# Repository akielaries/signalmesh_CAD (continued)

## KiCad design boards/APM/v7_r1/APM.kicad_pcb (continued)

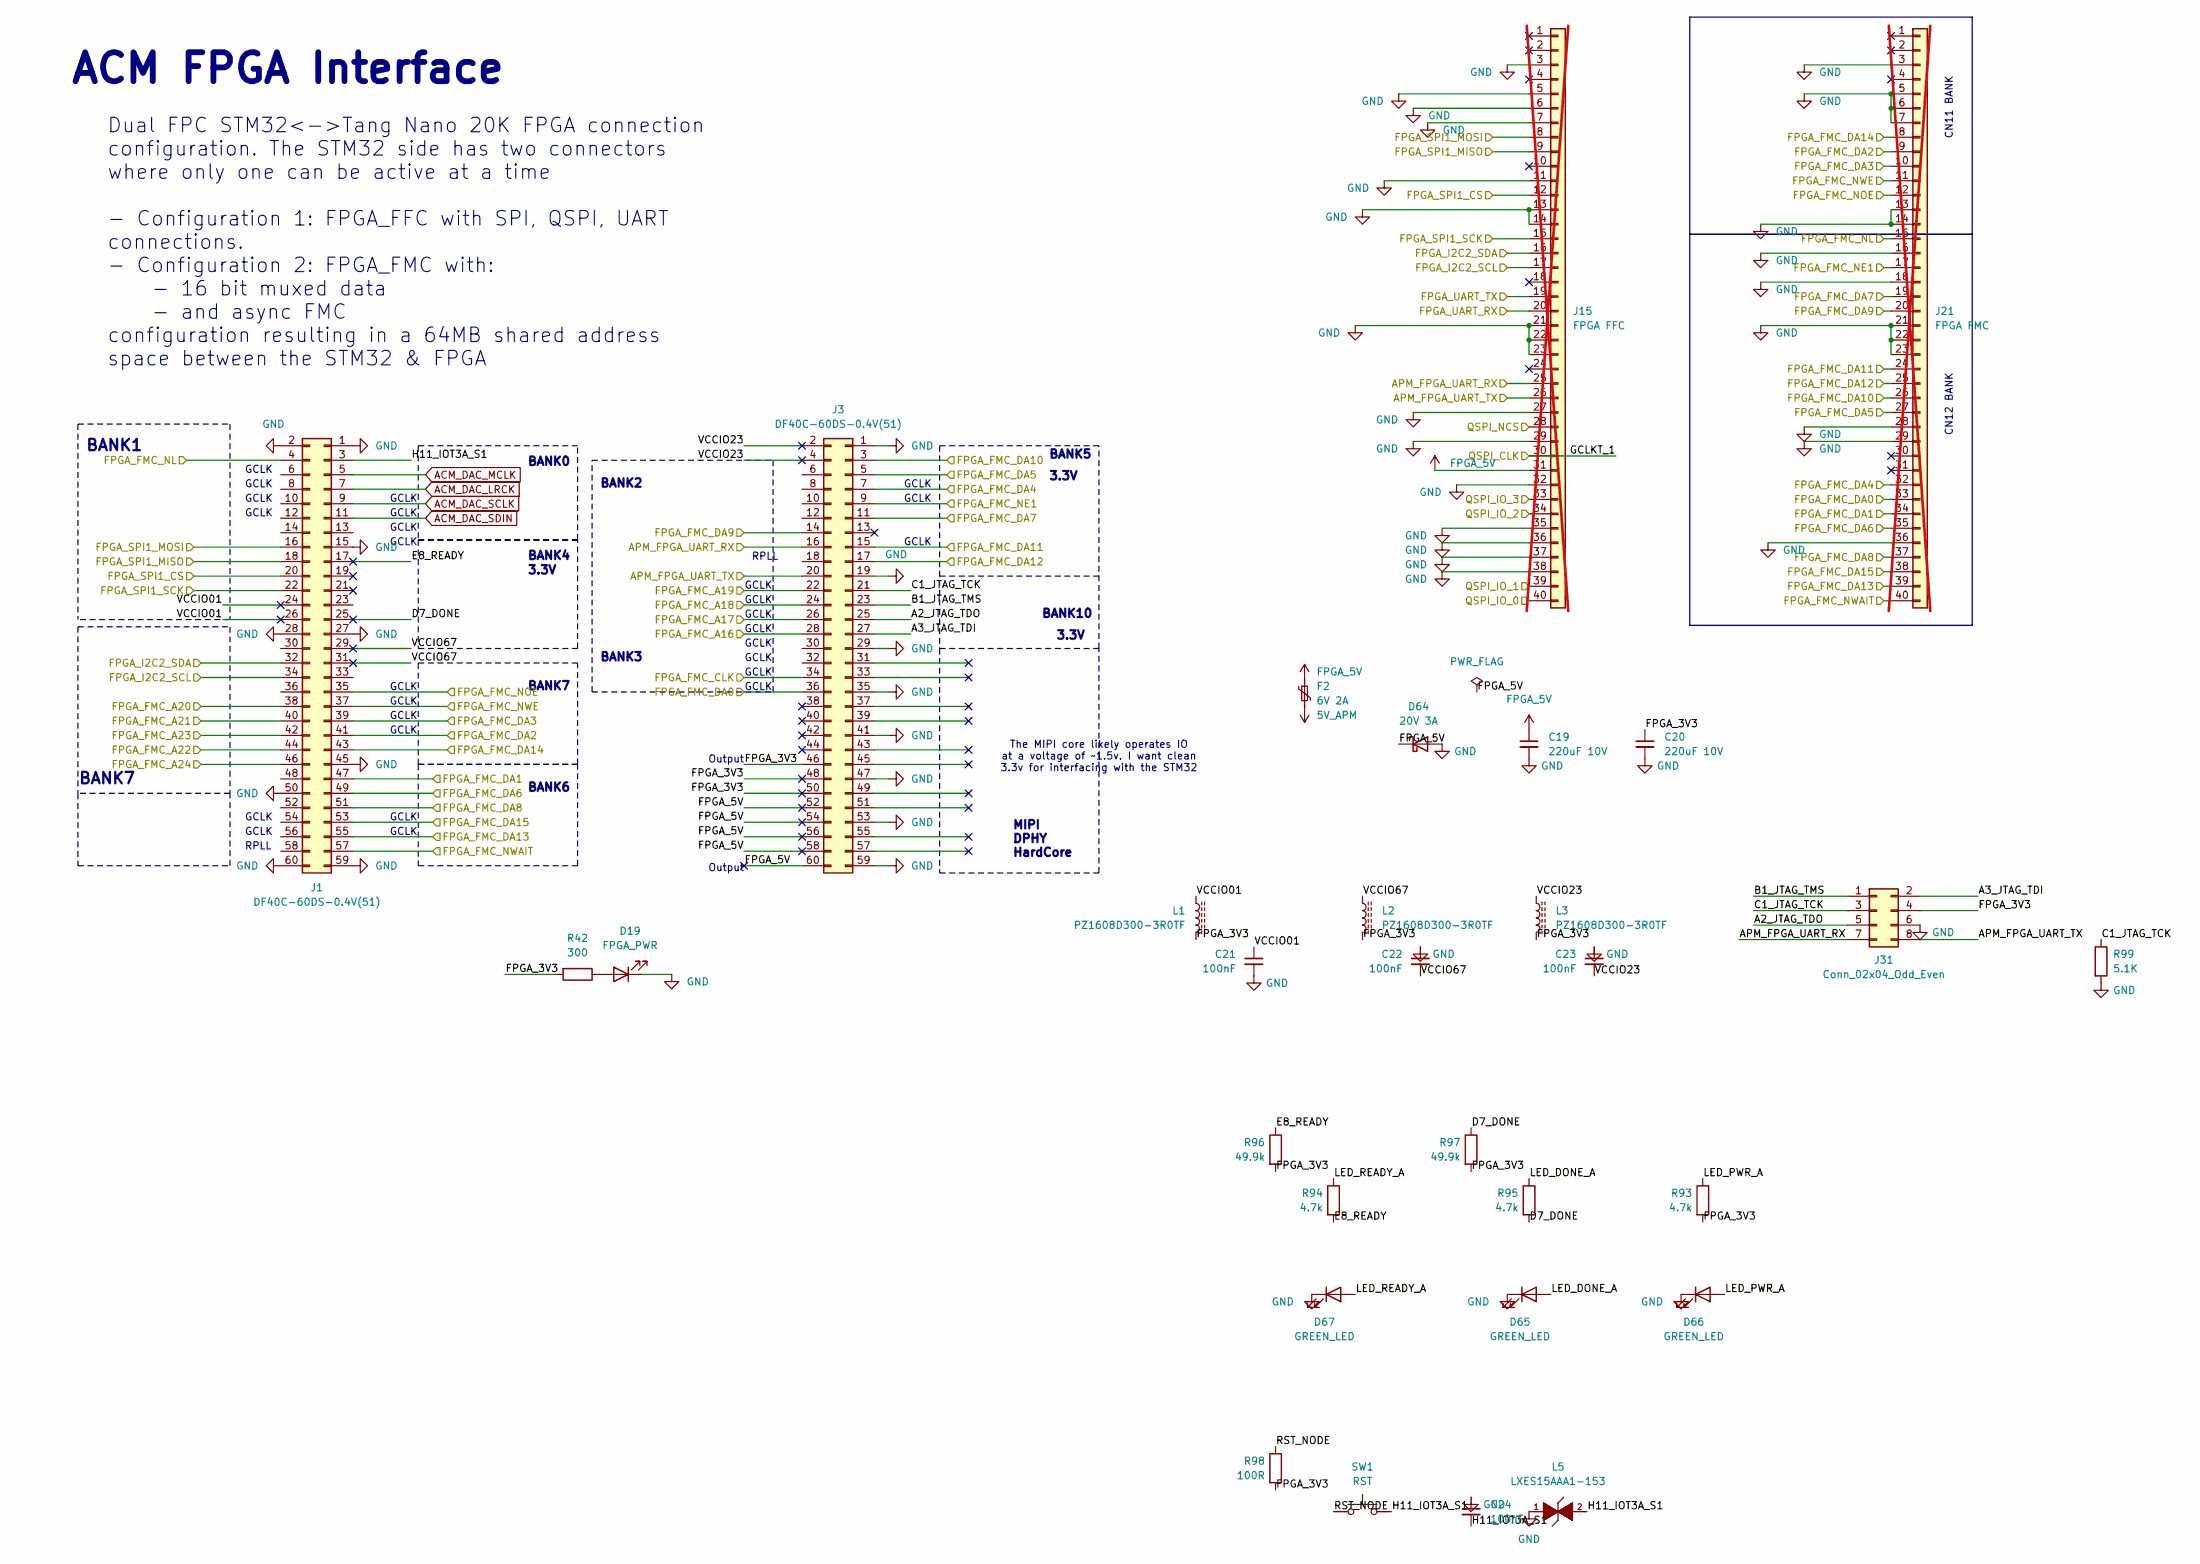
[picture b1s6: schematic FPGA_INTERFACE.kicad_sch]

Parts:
C19, C20: 220uF 10V; CP_Elec_4x3
C21, C22, C23, C24: 100nF; C_0402_1005Metric
D19: FPGA_PWR; LED_0603_1608Metric
D64: 20V 3A; D_SOD-123
D65, D66, D67: GREEN_LED; LED_0603_1608Metric
F2: 6V 2A; Fuse_0603_1608Metric
J1, J3: DF40C-60DS-0.4V(51); Hirose_DF40C-60DS-0.4V_2x30_P0.4mm
J15: FPGA FFC; Hirose_FH12-40S-0.5SH_1x40-1MP_P0.50mm_Horizontal; not fitted
J21: FPGA FMC; Hirose_FH12-40S-0.5SH_1x40-1MP_P0.50mm_Horizontal; not fitted
J31: Conn_02x04_Odd_Even; PinHeader_2x04_P2.54mm_Vertical_SMD
L1, L2, L3: PZ1608D300-3R0TF; L_0603_1608Metric
L5: LXES15AAA1-153; INDC1005X45
R42: 300; R_0201_0603Metric; DigiKey_Part_Number 311-10.0KCRCT-ND
R93, R94, R95: 4.7k; R_0201_0603Metric; DigiKey_Part_Number 311-10.0KCRCT-ND
R96, R97: 49.9k; R_0201_0603Metric; DigiKey_Part_Number 311-10.0KCRCT-ND
R98: 100R; R_0201_0603Metric; DigiKey_Part_Number 311-10.0KCRCT-ND
R99: 5.1K; R_0201_0603Metric; DigiKey_Part_Number 311-10.0KCRCT-ND
SW1: RST; SW_Push_1P1T_NO_CK_KMR2

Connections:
5V_APM: F2.2; also elsewhere on the board
/APM_FMC_A16: J3.28; also elsewhere on the board
/APM_FMC_A17: J3.26; also elsewhere on the board
/APM_FMC_A18: J3.24; also elsewhere on the board
/APM_FMC_A19: J3.22; also elsewhere on the board
/APM_FMC_A20: J1.38; also elsewhere on the board
/APM_FMC_A21: J1.40; also elsewhere on the board
/APM_FMC_A22: J1.44; also elsewhere on the board
/APM_FMC_A23: J1.42; also elsewhere on the board
/APM_FMC_A24: J1.46; also elsewhere on the board
/APM_FMC_CLK: J3.34; also elsewhere on the board
/APM_FMC_DA0: J3.36, J21.33; also elsewhere on the board
/APM_FMC_DA1: J1.47, J21.34; also elsewhere on the board
/APM_FMC_DA2: J1.41, J21.9; also elsewhere on the board
/APM_FMC_DA3: J1.39, J21.10; also elsewhere on the board
/APM_FMC_DA4: J3.7, J21.32; also elsewhere on the board
/APM_FMC_DA5: J3.5, J21.27; also elsewhere on the board
/APM_FMC_DA6: J1.49, J21.35; also elsewhere on the board
/APM_FMC_DA7: J3.11, J21.19; also elsewhere on the board
/APM_FMC_DA8: J1.51, J21.37; also elsewhere on the board
/APM_FMC_DA9: J3.14, J21.20; also elsewhere on the board
/APM_FMC_DA10: J3.3, J21.26; also elsewhere on the board
/APM_FMC_DA11: J3.15, J21.24; also elsewhere on the board
/APM_FMC_DA12: J3.17, J21.25; also elsewhere on the board
/APM_FMC_DA13: J1.55, J21.39; also elsewhere on the board
/APM_FMC_DA14: J1.43, J21.8; also elsewhere on the board
/APM_FMC_DA15: J1.53, J21.38; also elsewhere on the board
/APM_FMC_NE1: J3.9, J21.17; also elsewhere on the board
/APM_FMC_NL: J1.4, J21.15; also elsewhere on the board
/APM_FMC_NOE: J1.35, J21.12; also elsewhere on the board
/APM_FMC_NWAIT: J1.57, J21.40; also elsewhere on the board
/APM_FMC_NWE: J1.37, J21.11; also elsewhere on the board
/APM_FPGA_UART_RX: J3.16, J15.25, J31.7; also elsewhere on the board
/APM_FPGA_UART_TX: J3.20, J15.26, J31.8; also elsewhere on the board
/APM_I2C2_SCL: J1.34, J15.17; also elsewhere on the board
/APM_I2C2_SDA: J1.32, J15.16; also elsewhere on the board
/APM_SPI1_CS: J1.20, J15.12; also elsewhere on the board
/APM_SPI1_MISO: J1.18, J15.9; also elsewhere on the board
/APM_SPI1_MOSI: J1.16, J15.8; also elsewhere on the board
/APM_SPI1_SCK: J1.22, J15.15; also elsewhere on the board
/FPGA_INTERFACE/A2_JTAG_TDO: J3.25, J31.5
/FPGA_INTERFACE/A3_JTAG_TDI: J3.27, J31.2
/FPGA_INTERFACE/B1_JTAG_TMS: J3.23, J31.1
/FPGA_INTERFACE/C1_JTAG_TCK: J3.21, J31.3, R99.1
/FPGA_INTERFACE/D7_DONE: J1.25, R95.2, R97.1
/FPGA_INTERFACE/E8_READY: J1.17, R94.2, R96.1
/FPGA_INTERFACE/FPGA_3V3: C20.1, J3.46, J3.48, J3.50, J31.4, L1.2, L2.2, L3.2, R42.2, R93.2, R96.2, R97.2, R98.2
/FPGA_INTERFACE/H11_IOT3A_S1: C24.2, J1.3, L5.2, SW1.2
/FPGA_INTERFACE/LED_DONE_A: D65.2 (A), R95.1
/FPGA_INTERFACE/LED_PWR_A: D66.2 (A), R93.1
/FPGA_INTERFACE/LED_READY_A: D67.2 (A), R94.1
/FPGA_INTERFACE/RST_NODE: R98.1, SW1.1
/FPGA_INTERFACE/VCCIO01: C21.1, J1.24, J1.26, L1.1
/FPGA_INTERFACE/VCCIO23: C23.2, J3.2, J3.4, L3.1
/FPGA_INTERFACE/VCCIO67: C22.2, J1.29, J1.31, L2.1
ACM_DAC_LRCK: J1.7; also elsewhere on the board
ACM_DAC_MCLK: J1.5; also elsewhere on the board
ACM_DAC_SCLK: J1.9; also elsewhere on the board
ACM_DAC_SDIN: J1.11; also elsewhere on the board
FPGA_5V: C19.1, D64.1 (K), F2.1, J3.52, J3.54, J3.56, J3.58, J3.60, J15.31
GND: C19.2, C20.2, C21.2, C22.1, C23.1, C24.1, D19.1 (K), D64.2 (A), D65.1 (K), D66.1 (K), D67.1 (K), J1.1, J1.2, J1.15, J1.27, J1.28, J1.45, J1.50, J1.59, J1.60, J3.1, J3.19, J3.29, J3.35, J3.41, J3.47, J3.53, J3.59, J15.3, J15.5, J15.6, J15.7, J15.11, J15.13, J15.14, J15.21, J15.22, J15.23, J15.27, J15.29, J15.32, J15.35, J15.36, J15.37, J15.38, J21.3, J21.5, J21.6, J21.7, J21.13, J21.14, J21.16, J21.18, J21.21, J21.22, J21.23, J21.28, J21.29, J21.36, J31.6, L5.1, R99.2; also elsewhere on the board
unnamed: D19.2 (A), R42.1

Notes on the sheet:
BANK2
GCLK
BANK7
BANK3
Output
RPLL
ACM FPGA Interface
BANK10
The MIPI core likely operates IO at a voltage of ~1.5v. I want clean 3.3v for interfacing with the STM32
Dual FPC STM32<->Tang Nano 20K FPGA connection configuration. The STM32 side has two connectors where only one can be active at a time - Configuration 1: FPGA_FFC with SPI, QSPI, UART connections. - Configuration 2: FPGA_FMC with: - 16 bit muxed data - and async FMC configuration resulting in a 64M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
BANK0
CN11 BANK
BANK6
CN12 BANK
MIPI DPHY HardCore
3.3V
BANK1
BANK5
BANK4

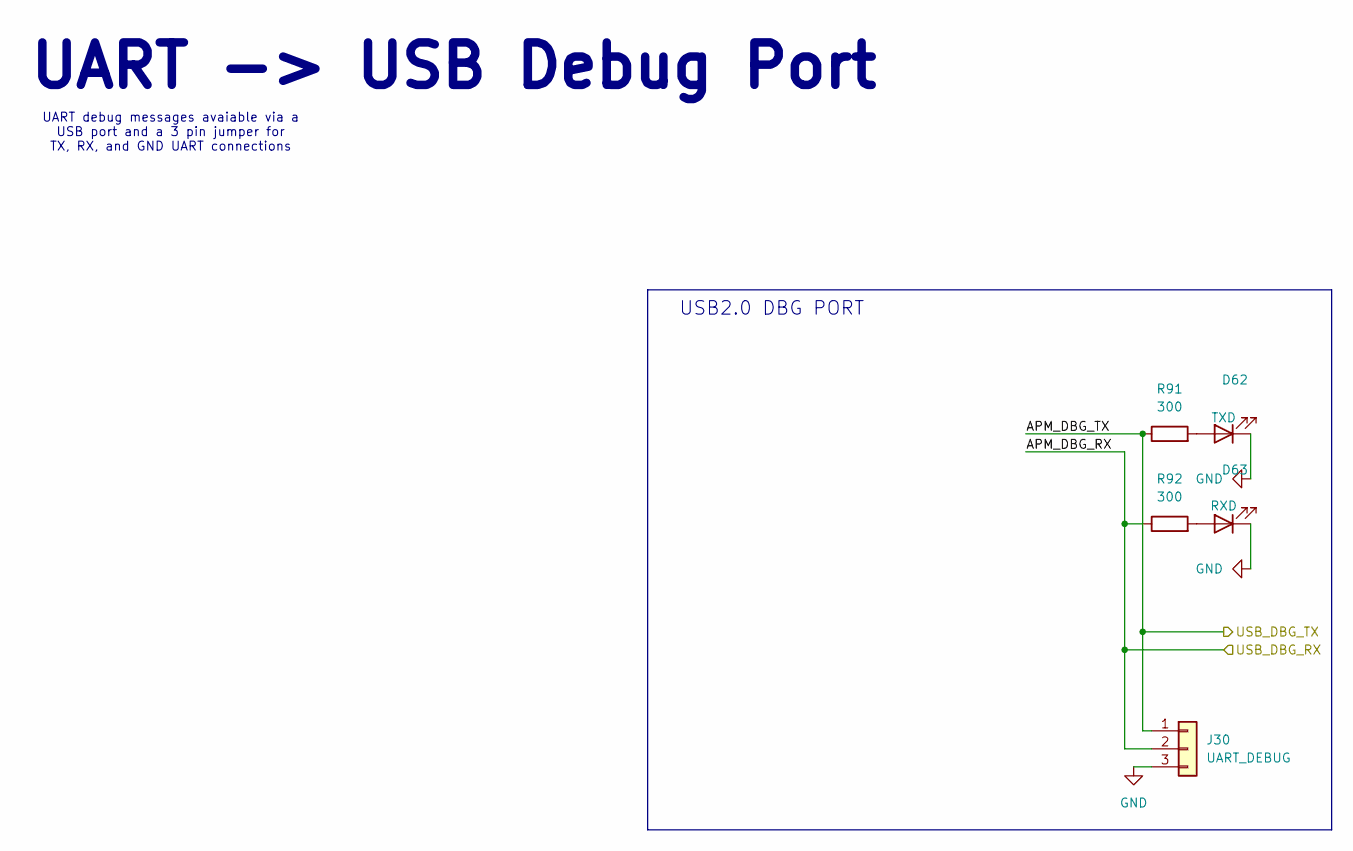
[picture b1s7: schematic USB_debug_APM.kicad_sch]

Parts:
D62: TXD; LED_0603_1608Metric
D63: RXD; LED_0603_1608Metric
J30: UART_DEBUG; PinHeader_1x03_P2.54mm_Vertical_SMD_Pin1Left
R91, R92: 300; R_0201_0603Metric; DigiKey_Part_Number 311-10.0KCRCT-ND

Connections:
/APM_DBG_RX: J30.2, R92.1; also elsewhere on the board
/APM_DBG_TX: J30.1, R91.1; also elsewhere on the board
GND: D62.1 (K), D63.1 (K), J30.3; also elsewhere on the board
unnamed: D62.2 (A), R91.2
unnamed: D63.2 (A), R92.2

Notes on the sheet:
UART -> USB Debug Port
USB2.0 DBG PORT
UART debug messages avaiable via a USB port and a 3 pin jumper for TX, RX, and GND UART connections

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
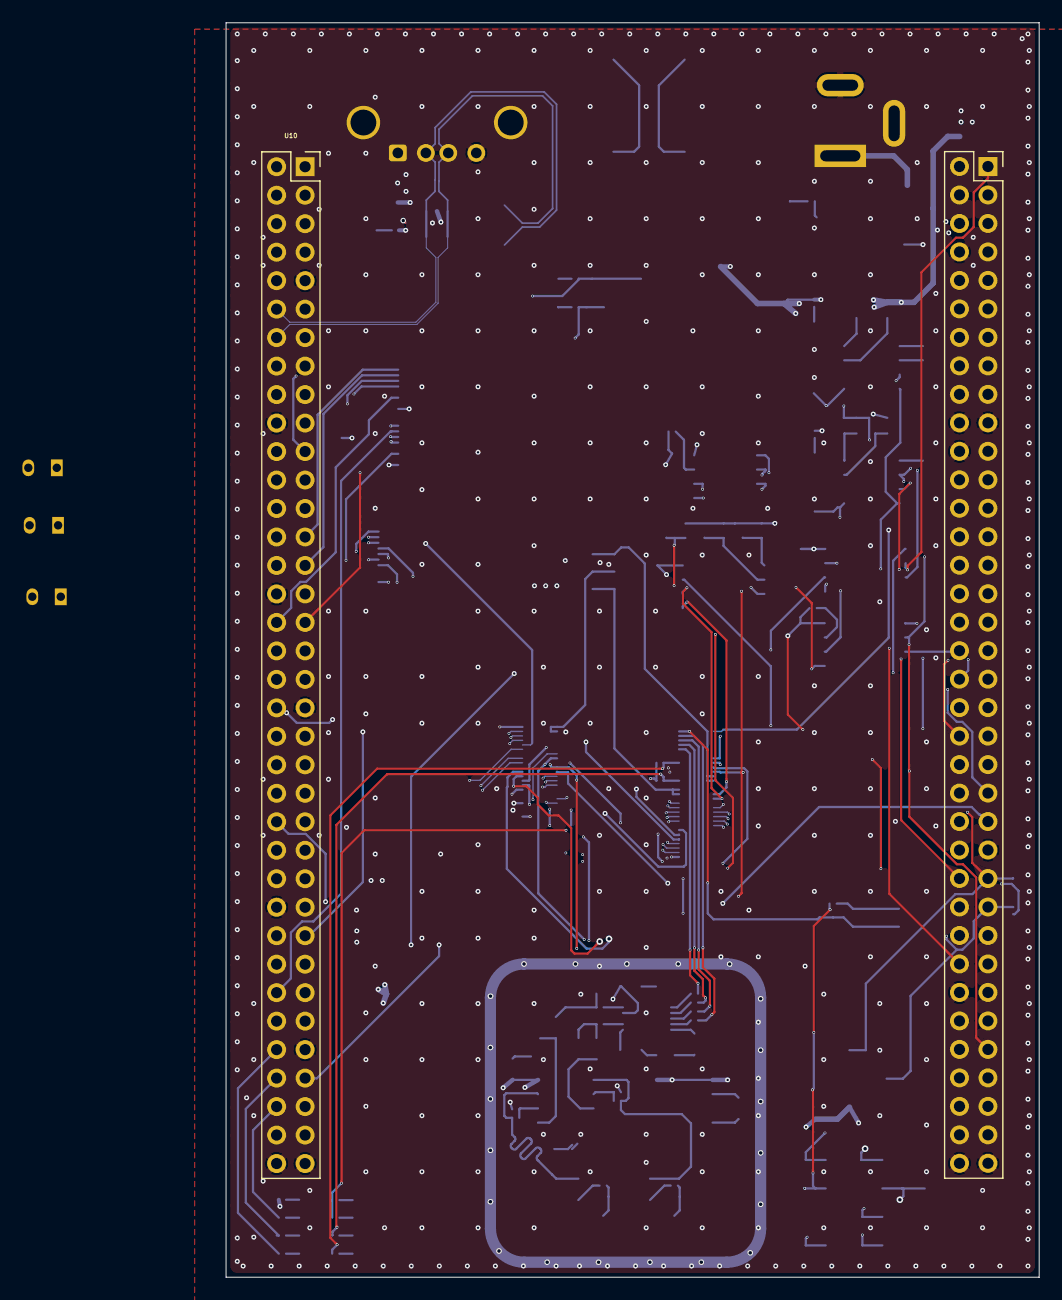
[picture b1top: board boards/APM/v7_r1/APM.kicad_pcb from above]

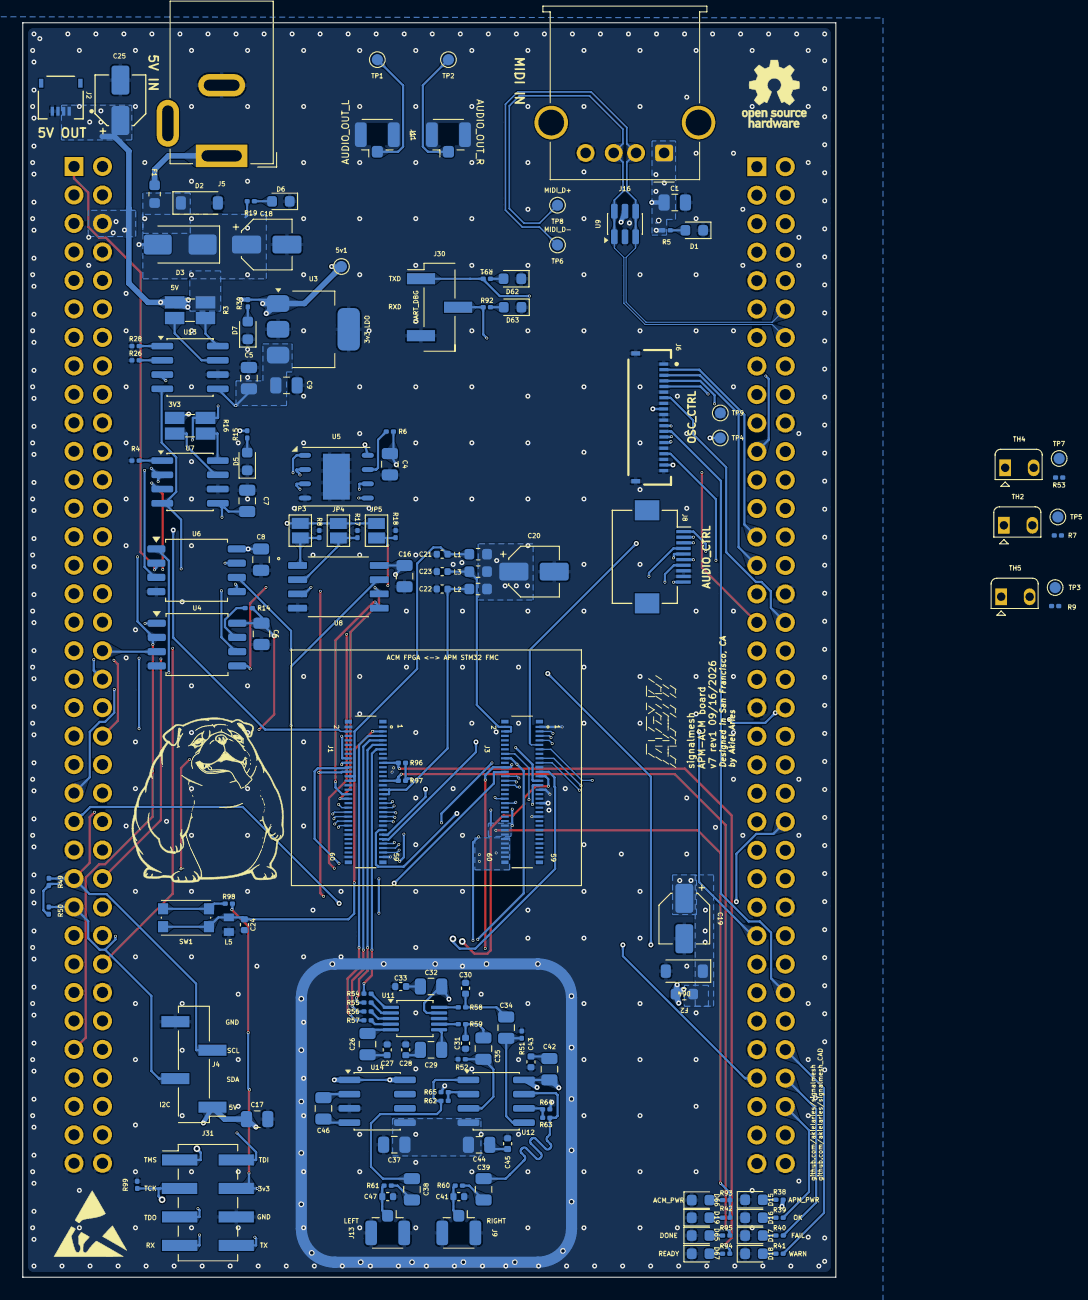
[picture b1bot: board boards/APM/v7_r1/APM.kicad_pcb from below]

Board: 6 copper layers, 72.5 x 111.9 mm, 151 parts (149 on the bottom side), 161 nets.

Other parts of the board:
C16: 100nF; C_0805_2012Metric
C18: 220uF 10V; CP_Elec_4x3
D2: 20V 3A; D_SOD-123
D3: SMAJ5.0A; D_SMA
D6: RED_LED_PWR; LED_0603_1608Metric
F1: 6V 2A; Fuse_0603_1608Metric
J5: Barrel_Jack; BarrelJack_GCT_DCJ200-10-A_Horizontal
R7, R9, R53: 10k; R_0201_0603Metric
R19: 4.7k; R_0201_0603Metric
TH2, TH4, TH5: 10k; Heraeus_TO-92-2

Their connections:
3V3_APM: C16.1; also elsewhere on the board
/THRM_A: R9.2; also elsewhere on the board
/THRM_C: R7.2; also elsewhere on the board
/THRM_E: R53.2; also elsewhere on the board
GND: C16.2, C18.2, D2.2 (A), D3.2 (A), D6.1 (K), J5.2, TH2.1, TH4.1, TH5.1; also elsewhere on the board
unnamed: D6.2 (A), R19.1
unnamed: F1.2, J5.1
unnamed: R7.1, TH2.2
unnamed: R9.1, TH5.2
unnamed: R53.1, TH4.2

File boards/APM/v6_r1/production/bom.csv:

Designator,Footprint,Quantity,Value,LCSC Part #
5V1,TestPoint_Pad_D1.0mm,1,5v,
C1,0805,1,22pf,
"C10, C12",0805,2,2.2nF,
"C11, C13",0805,2,4.7nF,
"C14, C15, C2",CP_Elec_4x3,3,10uF,
"C16, C17, C3, C4, C6, C8, C9",0805,7,100nF,
"C18, C19, C20, C25",CP_Elec_4x3,4,220uF 10V,
"C21, C22, C23, C24",0402,4,100nF,
"C5, C7",0805,2,0.1uf,
"D1, D5, D7",0603,3,LED_PWR,
D15,0603,1,PWR,
D16,0603,1,OK,
D17,0603,1,FAIL,
D18,0603,1,WARN,
D19,0603,1,FPGA_PWR,
"D2, D64",D_SOD-123,2,20V 3A,
D3,D_SMA,1,SMAJ5.0A,
D6,0603,1,RED_LED_PWR,
D62,0603,1,TXD,
D63,0603,1,RXD,
"D65, D66, D67",0603,3,GREEN_LED,
"F1, F2",0603,2,6V 2A,
"J1, J3",Hirose_DF40C-60DS-0.4V_2x30_P0.4mm,2,DF40C-60DS-0.4V(51),
J11,U.FL_Hirose_U.FL-R-SMT-1_Vertical,1,DAC_L_PRB,
J12,PinHeader_1x02_P2.54mm_Vertical,1,Conn_01x02,
J16,USB_A_Molex_67643_Horizontal,1,USB_A_FEMALE,
J19,Jack_3.5mm_Ledino_KB3SPRS_Horizontal,1,AudioPlug3,
J2,AMPHENOL_F3311A7H121004E200,1,AUDIO_PWR,
J23,PinHeader_1x03_P2.54mm_Vertical,1,VOL_L_CTRL,
J24,PinHeader_1x03_P2.54mm_Vertical,1,VOL_R_CTRL,
J30,PinHeader_1x03_P2.54mm_Vertical_SMD_Pin1Left,1,UART_DEBUG,
J31,PinHeader_2x04_P2.54mm_Vertical_SMD,1,Conn_02x04_Odd_Even,
J4,PinHeader_1x04_P2.54mm_Vertical_SMD_Pin1Left,1,LCD_display,
J5,BarrelJack_GCT_DCJ200-10-A_Horizontal,1,Barrel_Jack,
J6,GCT_FFC2B28-20-G,1,OSC_CTRL,
J7,U.FL_Hirose_U.FL-R-SMT-1_Vertical,1,DAC_R_PRB,
J8,Hirose_FH12-10S-0.5SH_1x10-1MP_P0.50mm_Horizontal,1,AUDIO_CTRL,
JP3,SolderJumper-2_P1.3mm_Open_Pad1.0x1.5mm,1,A0,
JP4,SolderJumper-2_P1.3mm_Open_Pad1.0x1.5mm,1,A1,
JP5,SolderJumper-2_P1.3mm_Open_Pad1.0x1.5mm,1,A2,
"L1, L2, L3",0603,3,PZ1608D300-3R0TF,
L5,INDC1005X45,1,LXES15AAA1-153,
"R14, R17, R18, R26, R28, R4, R53, R6, R7, R8, R9",0201,11,10k,
"R15, R30, R39, R40, R41, R42, R5, R91, R92",0201,9,300,
"R16, R3",R_Shunt_Ohmite_LVK12,2,0.1,
"R19, R93, R94, R95",0201,4,4.7k,
R38,0201,1,1.2k,
"R43, R44, R45, R46",0201,4,2.4k,
"R47, R48",0201,2,47,
"R49, R50",0201,2,2.2k,
"R96, R97",0201,2,49.9k,
R98,0201,1,100R,
R99,0201,1,5.1K,
SW1,SW_Push_1P1T_NO_CK_KMR2,1,RST,
"TH2, TH4, TH5",Heraeus_TO-92-2,3,10k,
TP3,TestPoint_Pad_D1.0mm,1,THRM_A,
TP4,TestPoint_Pad_D1.0mm,1,FPC_3V3_TP,
TP5,TestPoint_Pad_D1.0mm,1,THRM_C,
TP6,TestPoint_Pad_D1.0mm,1,MIDI_D-,
TP7,TestPoint_Pad_D1.0mm,1,THRM_E,
TP8,TestPoint_Pad_D1.0mm,1,MIDI_D+,
TP9,TestPoint_Pad_D1.0mm,1,FPC_GND_TP,
"U1, U10",PinSocket_2x36_P2.54mm_Vertical,2,~,
"U13, U7",SOIC-8_3.9x4.9mm_P1.27mm,2,INA219AxD,
U2,DIP-8_W7.62mm_SMDSocket_SmallPads,1,OPA1678,
U3,SOT-223-3_TabPin2,1,LT1963AxST-3.3,
"U4, U6",SOIC-8_5.3x5.3mm_P1.27mm,2,W25Q128JVS,
U5,DFN-S-8-1EP_6x5mm_P1.27mm,1,MR25H40,
U8,SOIC127P794X202-8N,1,24LC1025-I_P,
U9,SOT-23-6,1,USBLC6-2SC6,

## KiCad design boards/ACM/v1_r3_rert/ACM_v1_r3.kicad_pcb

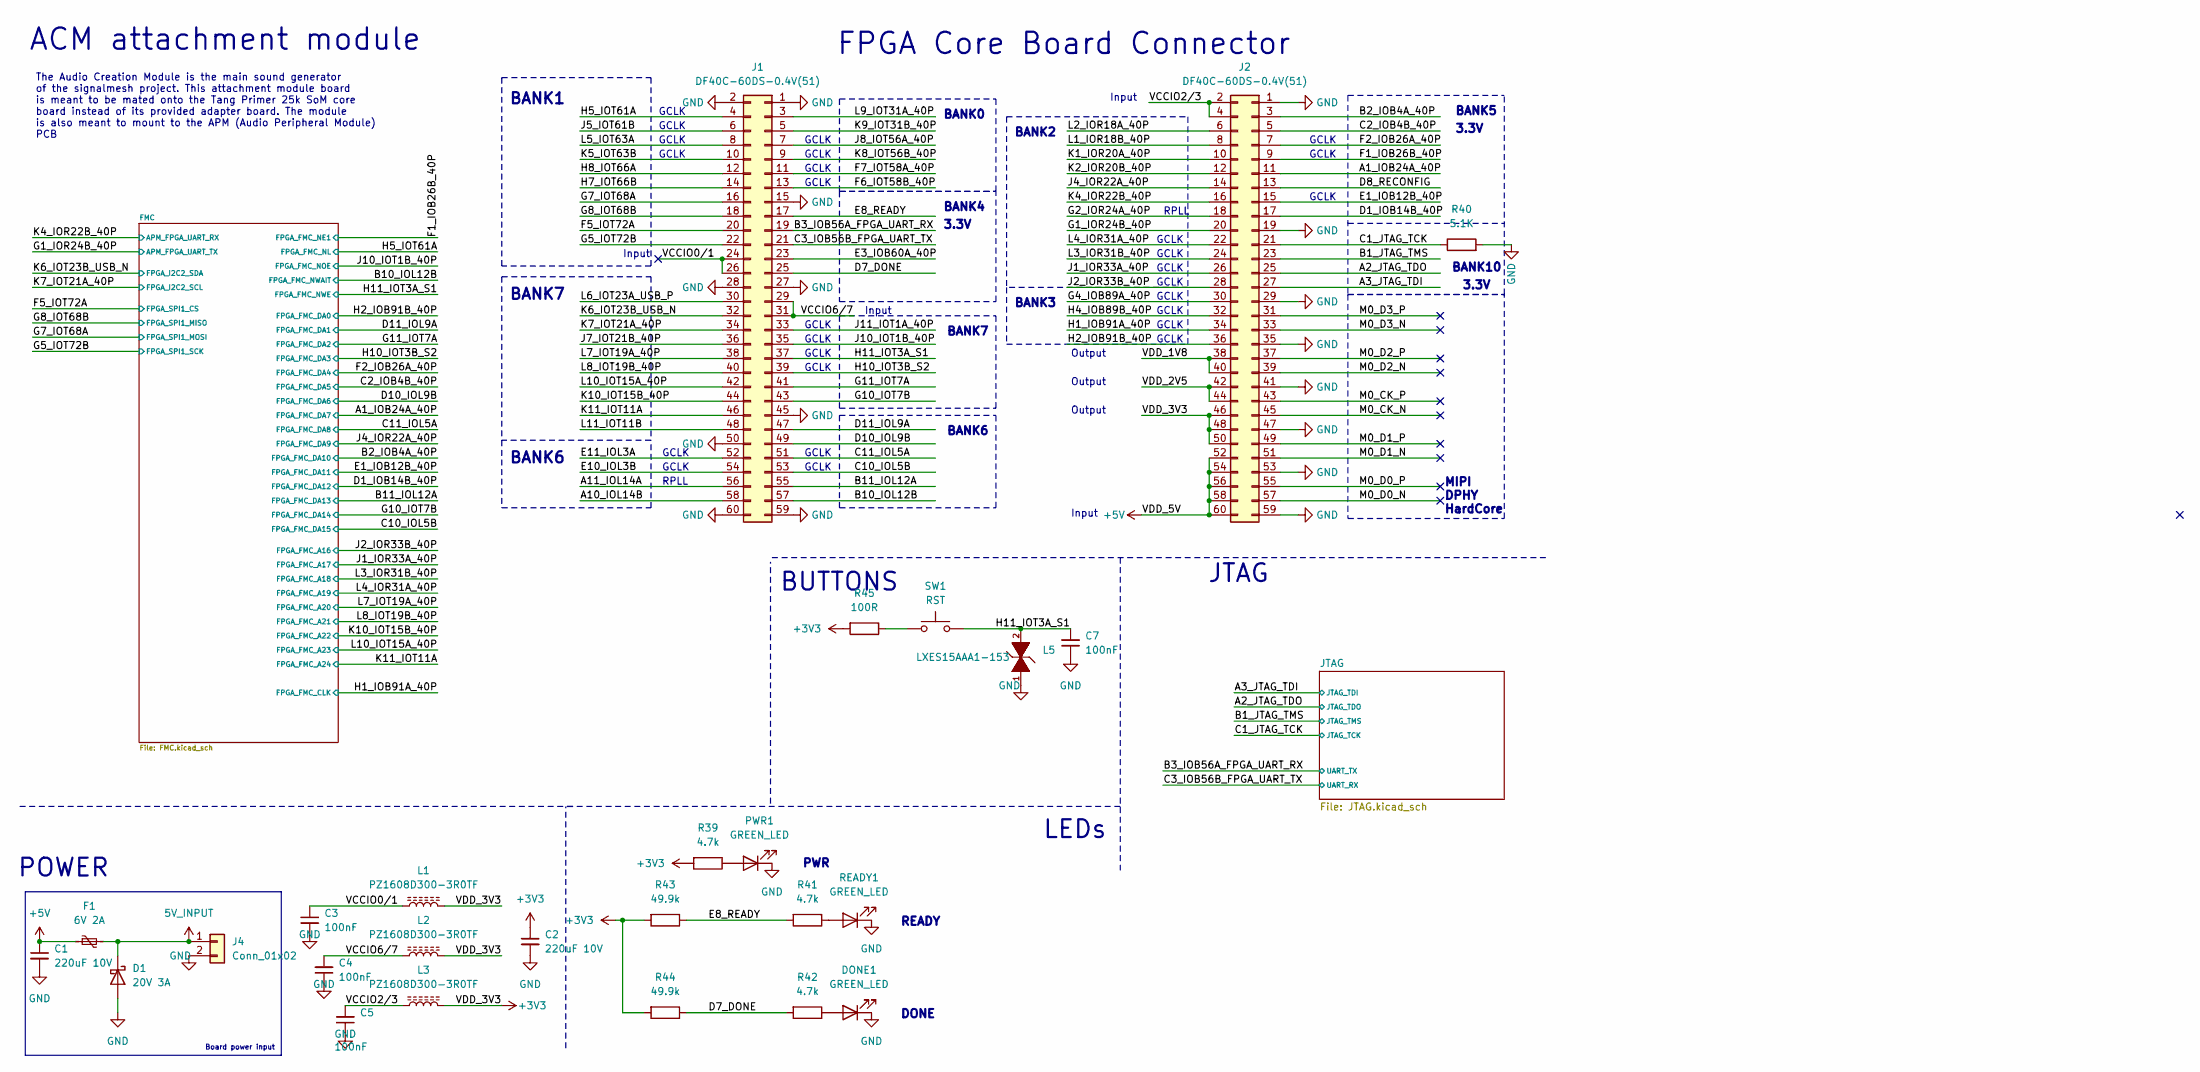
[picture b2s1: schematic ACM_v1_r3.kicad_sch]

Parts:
C1, C2: 220uF 10V; CP_Elec_4x3
C3, C4, C5, C7: 100nF; C_0402_1005Metric
D1: 20V 3A; D_SOD-123
DONE1: GREEN_LED; LED_0603_1608Metric
F1: 6V 2A; Fuse_0603_1608Metric
J1, J2: DF40C-60DS-0.4V(51); Hirose_DF40C-60DS-0.4V_2x30_P0.4mm
J4: Conn_01x02; PinSocket_1x02_P2.54mm_Vertical_SMD_Pin1Left
L1, L2, L3: PZ1608D300-3R0TF; L_0603_1608Metric
L5: LXES15AAA1-153; INDC1005X45
PWR1: GREEN_LED; LED_0603_1608Metric
R39, R41, R42: 4.7k; R_0201_0603Metric; DigiKey_Part_Number 311-10.0KCRCT-ND
R40: 5.1K; R_0201_0603Metric; DigiKey_Part_Number 311-10.0KCRCT-ND
R43, R44: 49.9k; R_0201_0603Metric; DigiKey_Part_Number 311-10.0KCRCT-ND
R45: 100R; R_0201_0603Metric; DigiKey_Part_Number 311-10.0KCRCT-ND
READY1: GREEN_LED; LED_0603_1608Metric
SW1: RST; SW_Push_1P1T_NO_CK_KMR2

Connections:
5V_INPUT: D1.1 (K), F1.2, J4.1
+3V3: C2.1, J2.46, J2.48, J2.50, L1.2, L2.2, L3.2, R39.2, R43.2, R44.2, R45.2; also elsewhere on the board
+5V: C1.1, F1.1, J2.52, J2.54, J2.56, J2.58, J2.60; also elsewhere on the board
/A1_IOB24A_40P: J2.11; also elsewhere on the board
/A2_JTAG_TDO: J2.25; also elsewhere on the board
/A3_JTAG_TDI: J2.27; also elsewhere on the board
/A10_IOL14B: J1.58
/A11_IOL14A: J1.56
/B1_JTAG_TMS: J2.23; also elsewhere on the board
/B2_IOB4A_40P: J2.3; also elsewhere on the board
/B3_IOB56A_FPGA_UART_RX: J1.19; also elsewhere on the board
/B10_IOL12B: J1.57; also elsewhere on the board
/B11_IOL12A: J1.55; also elsewhere on the board
/C1_JTAG_TCK: J2.21, R40.1; also elsewhere on the board
/C2_IOB4B_40P: J2.5; also elsewhere on the board
/C3_IOB56B_FPGA_UART_TX: J1.21; also elsewhere on the board
/C10_IOL5B: J1.53; also elsewhere on the board
/C11_IOL5A: J1.51; also elsewhere on the board
/D1_IOB14B_40P: J2.17; also elsewhere on the board
/D7_DONE: J1.25, R42.2, R44.1
/D8_RECONFIG: J2.13
/D10_IOL9B: J1.49; also elsewhere on the board
/D11_IOL9A: J1.47; also elsewhere on the board
/E1_IOB12B_40P: J2.15; also elsewhere on the board
/E3_IOB60A_40P: J1.23
/E8_READY: J1.17, R41.2, R43.1
/E10_IOL3B: J1.54
/E11_IOL3A: J1.52
/F1_IOB26B_40P: J2.9; also elsewhere on the board
/F2_IOB26A_40P: J2.7; also elsewhere on the board
/F5_IOT72A: J1.20; also elsewhere on the board
/F6_IOT58B_40P: J1.13
/F7_IOT58A_40P: J1.11
/G1_IOR24B_40P: J2.20; also elsewhere on the board
/G2_IOR24A_40P: J2.18
/G4_IOB89A_40P: J2.30
/G5_IOT72B: J1.22; also elsewhere on the board
/G7_IOT68A: J1.16; also elsewhere on the board
/G8_IOT68B: J1.18; also elsewhere on the board
/G10_IOT7B: J1.43; also elsewhere on the board
/G11_IOT7A: J1.41; also elsewhere on the board
/H1_IOB91A_40P: J2.34; also elsewhere on the board
/H2_IOB91B_40P: J2.36; also elsewhere on the board
/H4_IOB89B_40P: J2.32
/H5_IOT61A: J1.4; also elsewhere on the board
/H7_IOT66B: J1.14
/H8_IOT66A: J1.12
/H10_IOT3B_S2: J1.39; also elsewhere on the board
/H11_IOT3A_S1: C7.2, J1.37, L5.2, SW1.2; also elsewhere on the board
/J1_IOR33A_40P: J2.26; also elsewhere on the board
/J2_IOR33B_40P: J2.28; also elsewhere on the board
/J4_IOR22A_40P: J2.14; also elsewhere on the board
/J5_IOT61B: J1.6
/J7_IOT21B_40P: J1.36
/J8_IOT56A_40P: J1.7
/J10_IOT1B_40P: J1.35; also elsewhere on the board
/J11_IOT1A_40P: J1.33
/K1_IOR20A_40P: J2.10
/K2_IOR20B_40P: J2.12
/K4_IOR22B_40P: J2.16; also elsewhere on the board
/K5_IOT63B: J1.10
/K6_IOT23B_USB_N: J1.32; also elsewhere on the board
/K7_IOT21A_40P: J1.34; also elsewhere on the board
/K8_IOT56B_40P: J1.9
/K9_IOT31B_40P: J1.5
/K10_IOT15B_40P: J1.44; also elsewhere on the board
/K11_IOT11A: J1.46; also elsewhere on the board
/L1_IOR18B_40P: J2.8
/L2_IOR18A_40P: J2.6
/L3_IOR31B_40P: J2.24; also elsewhere on the board
/L4_IOR31A_40P: J2.22; also elsewhere on the board
/L5_IOT63A: J1.8
/L6_IOT23A_USB_P: J1.30
/L7_IOT19A_40P: J1.38; also elsewhere on the board
/L8_IOT19B_40P: J1.40; also elsewhere on the board
/L9_IOT31A_40P: J1.3
/L10_IOT15A_40P: J1.42; also elsewhere on the board
/L11_IOT11B: J1.48
/M0_CK_N: J2.45
/M0_CK_P: J2.43
/M0_D0_N: J2.57
/M0_D0_P: J2.55
/M0_D1_N: J2.51
/M0_D1_P: J2.49
/M0_D2_N: J2.39
/M0_D2_P: J2.37
/M0_D3_N: J2.33
/M0_D3_P: J2.31
/VCCIO0/1: C3.1, J1.24, J1.26, L1.1
/VCCIO2/3: C5.2, J2.2, J2.4, L3.1
/VCCIO6/7: C4.2, J1.29, J1.31, L2.1
/VDD_1V8: J2.38, J2.40
/VDD_2V5: J2.42, J2.44
GND: C1.2, C2.2, C3.2, C4.1, C5.1, C7.1, D1.2 (A), DONE1.1 (K), J1.1, J1.2, J1.15, J1.27, J1.28, J1.45, J1.50, J1.59, J1.60, J2.1, J2.19, J2.29, J2.35, J2.41, J2.47, J2.53, J2.59, J4.2, L5.1, PWR1.1 (K), R40.2, READY1.1 (K); also elsewhere on the board
unnamed: DONE1.2 (A), R42.1
unnamed: PWR1.2 (A), R39.1
unnamed: R45.1, SW1.1
unnamed: R41.1, READY1.2 (A)

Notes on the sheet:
3.3V
GCLK
Input
BANK5
POWER
BANK6
BANK7
Output
LEDs
READY
BANK3
FPGA Core Board Connector
BANK1
BANK10
JTAG
BANK2
Board power input
BUTTONS
BANK4
PWR
ACM attachment module
The Audio Creation Module is the main sound generator of the signalmesh project. This attachment module board is meant to be mated onto the Tang Primer 25k SoM core board instead of its provided adapter board. The module is also meant to mount to the APM (Audio Peripheral Module) PCB
DONE
BANK0
RPLL
MIPI DPHY HardCore

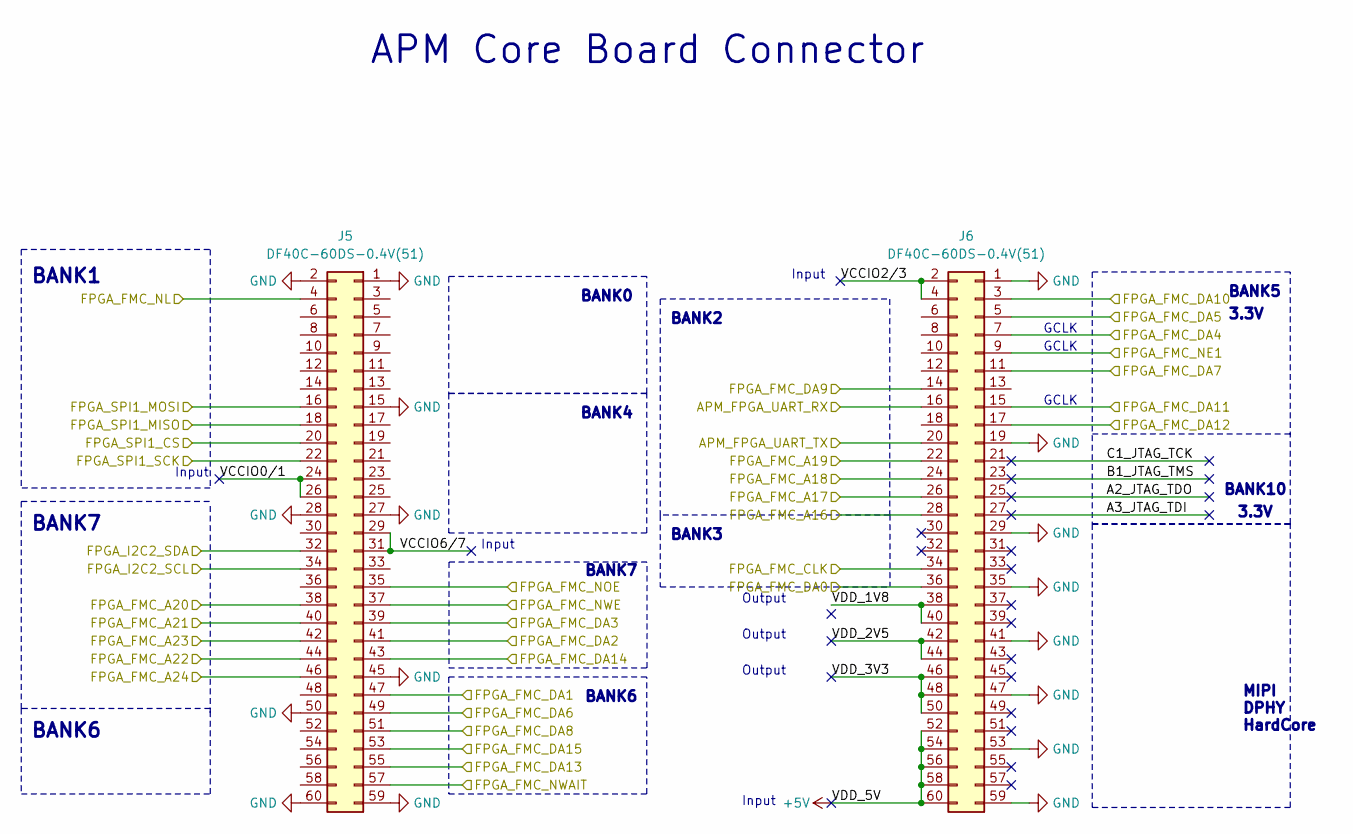
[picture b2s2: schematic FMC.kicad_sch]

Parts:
J5, J6: DF40C-60DS-0.4V(51); Hirose_DF40C-60DS-0.4V_2x30_P0.4mm

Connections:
+5V: J6.52, J6.54, J6.56, J6.58, J6.60; also elsewhere on the board
/A1_IOB24A_40P: J6.11; also elsewhere on the board
/B2_IOB4A_40P: J6.3; also elsewhere on the board
/B10_IOL12B: J5.57; also elsewhere on the board
/B11_IOL12A: J5.55; also elsewhere on the board
/C2_IOB4B_40P: J6.5; also elsewhere on the board
/C10_IOL5B: J5.53; also elsewhere on the board
/C11_IOL5A: J5.51; also elsewhere on the board
/D1_IOB14B_40P: J6.17; also elsewhere on the board
/D10_IOL9B: J5.49; also elsewhere on the board
/D11_IOL9A: J5.47; also elsewhere on the board
/E1_IOB12B_40P: J6.15; also elsewhere on the board
/F1_IOB26B_40P: J6.9; also elsewhere on the board
/F2_IOB26A_40P: J6.7; also elsewhere on the board
/F5_IOT72A: J5.20; also elsewhere on the board
/FMC/A2_JTAG_TDO: J6.25
/FMC/A3_JTAG_TDI: J6.27
/FMC/B1_JTAG_TMS: J6.23
/FMC/C1_JTAG_TCK: J6.21
/FMC/VCCIO0/1: J5.24, J5.26
/FMC/VCCIO2/3: J6.2, J6.4
/FMC/VCCIO6/7: J5.29, J5.31
/FMC/VDD_1V8: J6.38, J6.40
/FMC/VDD_2V5: J6.42, J6.44
/FMC/VDD_3V3: J6.46, J6.48, J6.50
/G1_IOR24B_40P: J6.20; also elsewhere on the board
/G5_IOT72B: J5.22; also elsewhere on the board
/G7_IOT68A: J5.16; also elsewhere on the board
/G8_IOT68B: J5.18; also elsewhere on the board
/G10_IOT7B: J5.43; also elsewhere on the board
/G11_IOT7A: J5.41; also elsewhere on the board
/H1_IOB91A_40P: J6.34; also elsewhere on the board
/H2_IOB91B_40P: J6.36; also elsewhere on the board
/H5_IOT61A: J5.4; also elsewhere on the board
/H10_IOT3B_S2: J5.39; also elsewhere on the board
/H11_IOT3A_S1: J5.37; also elsewhere on the board
/J1_IOR33A_40P: J6.26; also elsewhere on the board
/J2_IOR33B_40P: J6.28; also elsewhere on the board
/J4_IOR22A_40P: J6.14; also elsewhere on the board
/J10_IOT1B_40P: J5.35; also elsewhere on the board
/K4_IOR22B_40P: J6.16; also elsewhere on the board
/K6_IOT23B_USB_N: J5.32; also elsewhere on the board
/K7_IOT21A_40P: J5.34; also elsewhere on the board
/K10_IOT15B_40P: J5.44; also elsewhere on the board
/K11_IOT11A: J5.46; also elsewhere on the board
/L3_IOR31B_40P: J6.24; also elsewhere on the board
/L4_IOR31A_40P: J6.22; also elsewhere on the board
/L7_IOT19A_40P: J5.38; also elsewhere on the board
/L8_IOT19B_40P: J5.40; also elsewhere on the board
/L10_IOT15A_40P: J5.42; also elsewhere on the board
GND: J5.1, J5.2, J5.15, J5.27, J5.28, J5.45, J5.50, J5.59, J5.60, J6.1, J6.19, J6.29, J6.35, J6.41, J6.47, J6.53, J6.59; also elsewhere on the board

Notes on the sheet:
BANK2
MIPI DPHY HardCore
BANK0
APM Core Board Connector
BANK3
BANK5
GCLK
BANK6
BANK7
Input
Output
BANK4
3.3V
BANK1
BANK10

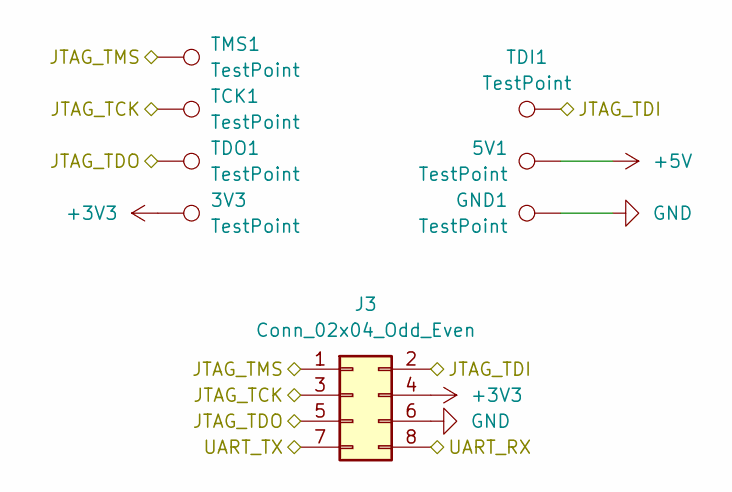
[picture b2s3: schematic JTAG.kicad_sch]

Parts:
3V3, 5V1: TestPoint; TestPoint_Pad_D1.0mm
GND1: TestPoint; TestPoint_Pad_D1.0mm
J3: Conn_02x04_Odd_Even; PinHeader_2x04_P2.54mm_Vertical_SMD
TCK1: TestPoint; TestPoint_Pad_D1.0mm
TDI1: TestPoint; TestPoint_Pad_D1.0mm
TDO1: TestPoint; TestPoint_Pad_D1.0mm
TMS1: TestPoint; TestPoint_Pad_D1.0mm

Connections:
+3V3: 3V3.1 (1_1), J3.4; also elsewhere on the board
+5V: 5V1.1 (1_1); also elsewhere on the board
/A2_JTAG_TDO: J3.5, TDO1.1 (1_1); also elsewhere on the board
/A3_JTAG_TDI: J3.2, TDI1.1 (1_1); also elsewhere on the board
/B1_JTAG_TMS: J3.1, TMS1.1 (1_1); also elsewhere on the board
/B3_IOB56A_FPGA_UART_RX: J3.7; also elsewhere on the board
/C1_JTAG_TCK: J3.3, TCK1.1 (1_1); also elsewhere on the board
/C3_IOB56B_FPGA_UART_TX: J3.8; also elsewhere on the board
GND: GND1.1 (1_1), J3.6; also elsewhere on the board
